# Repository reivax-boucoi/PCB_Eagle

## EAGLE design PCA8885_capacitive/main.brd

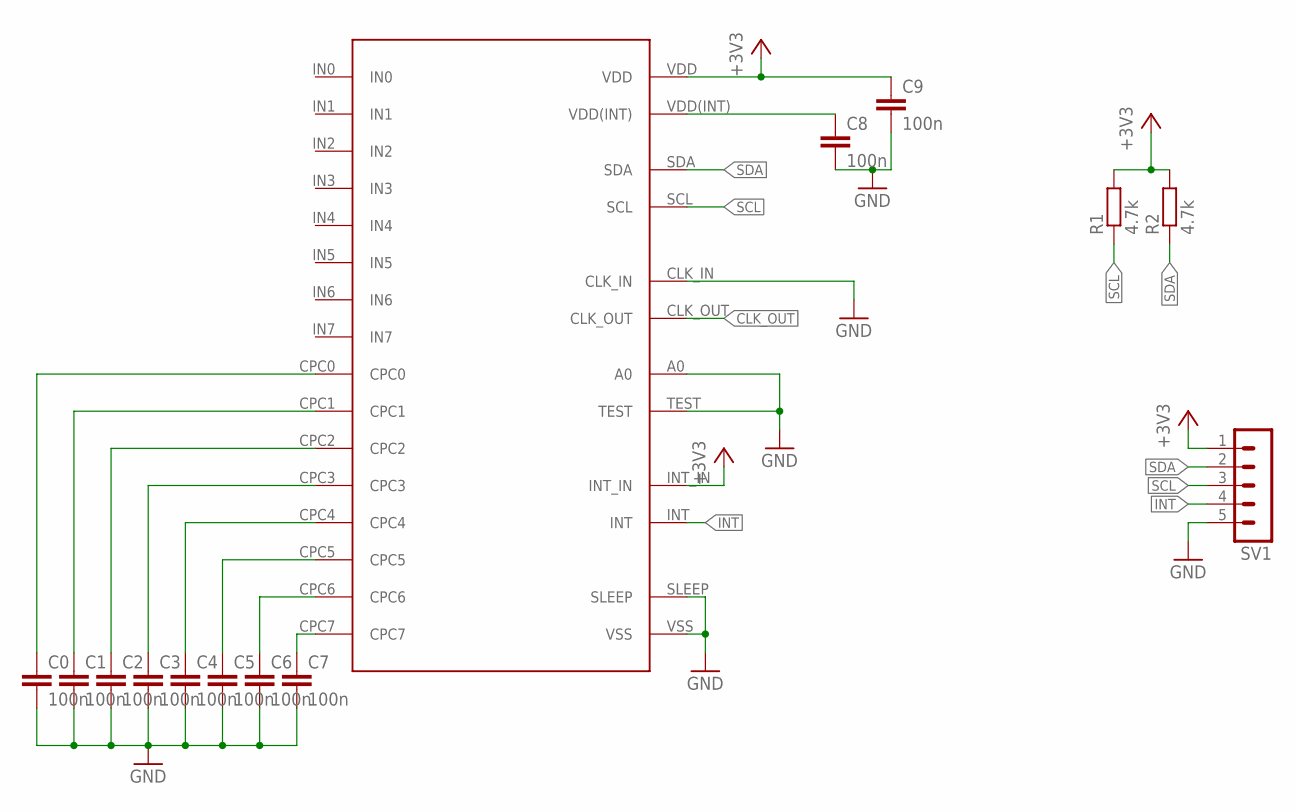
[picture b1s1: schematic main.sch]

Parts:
C0, C1, C2, C3, C4, C5, C6, C7, C8, C9: 100n; C0402
R1, R2: 4.7k; R0603
SV1: MA05-1
U$1: PCA8885; TSSOP28

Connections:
+3V3: C9.1, R1.2, R2.2, SV1.1, U$1.INT_IN, U$1.VDD
CLK_OUT: U$1.CLK_OUT
GND: C0.2, C1.2, C2.2, C3.2, C4.2, C5.2, C6.2, C7.2, C8.2, C9.2, SV1.5, U$1.A0, U$1.CLK_IN, U$1.SLEEP, U$1.TEST, U$1.VSS
INT: SV1.4, U$1.INT
unnamed: C7.1, U$1.CPC7
unnamed: C6.1, U$1.CPC6
unnamed: C5.1, U$1.CPC5
unnamed: C4.1, U$1.CPC4
unnamed: C3.1, U$1.CPC3
unnamed: C2.1, U$1.CPC2
unnamed: C1.1, U$1.CPC1
unnamed: C0.1, U$1.CPC0
unnamed: C8.1, U$1.VDD(INT)
SCL: R1.1, SV1.3, U$1.SCL
SDA: R2.1, SV1.2, U$1.SDA

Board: 2 copper layers, 14 parts (0 on the bottom side), 14 nets, no tracks yet.

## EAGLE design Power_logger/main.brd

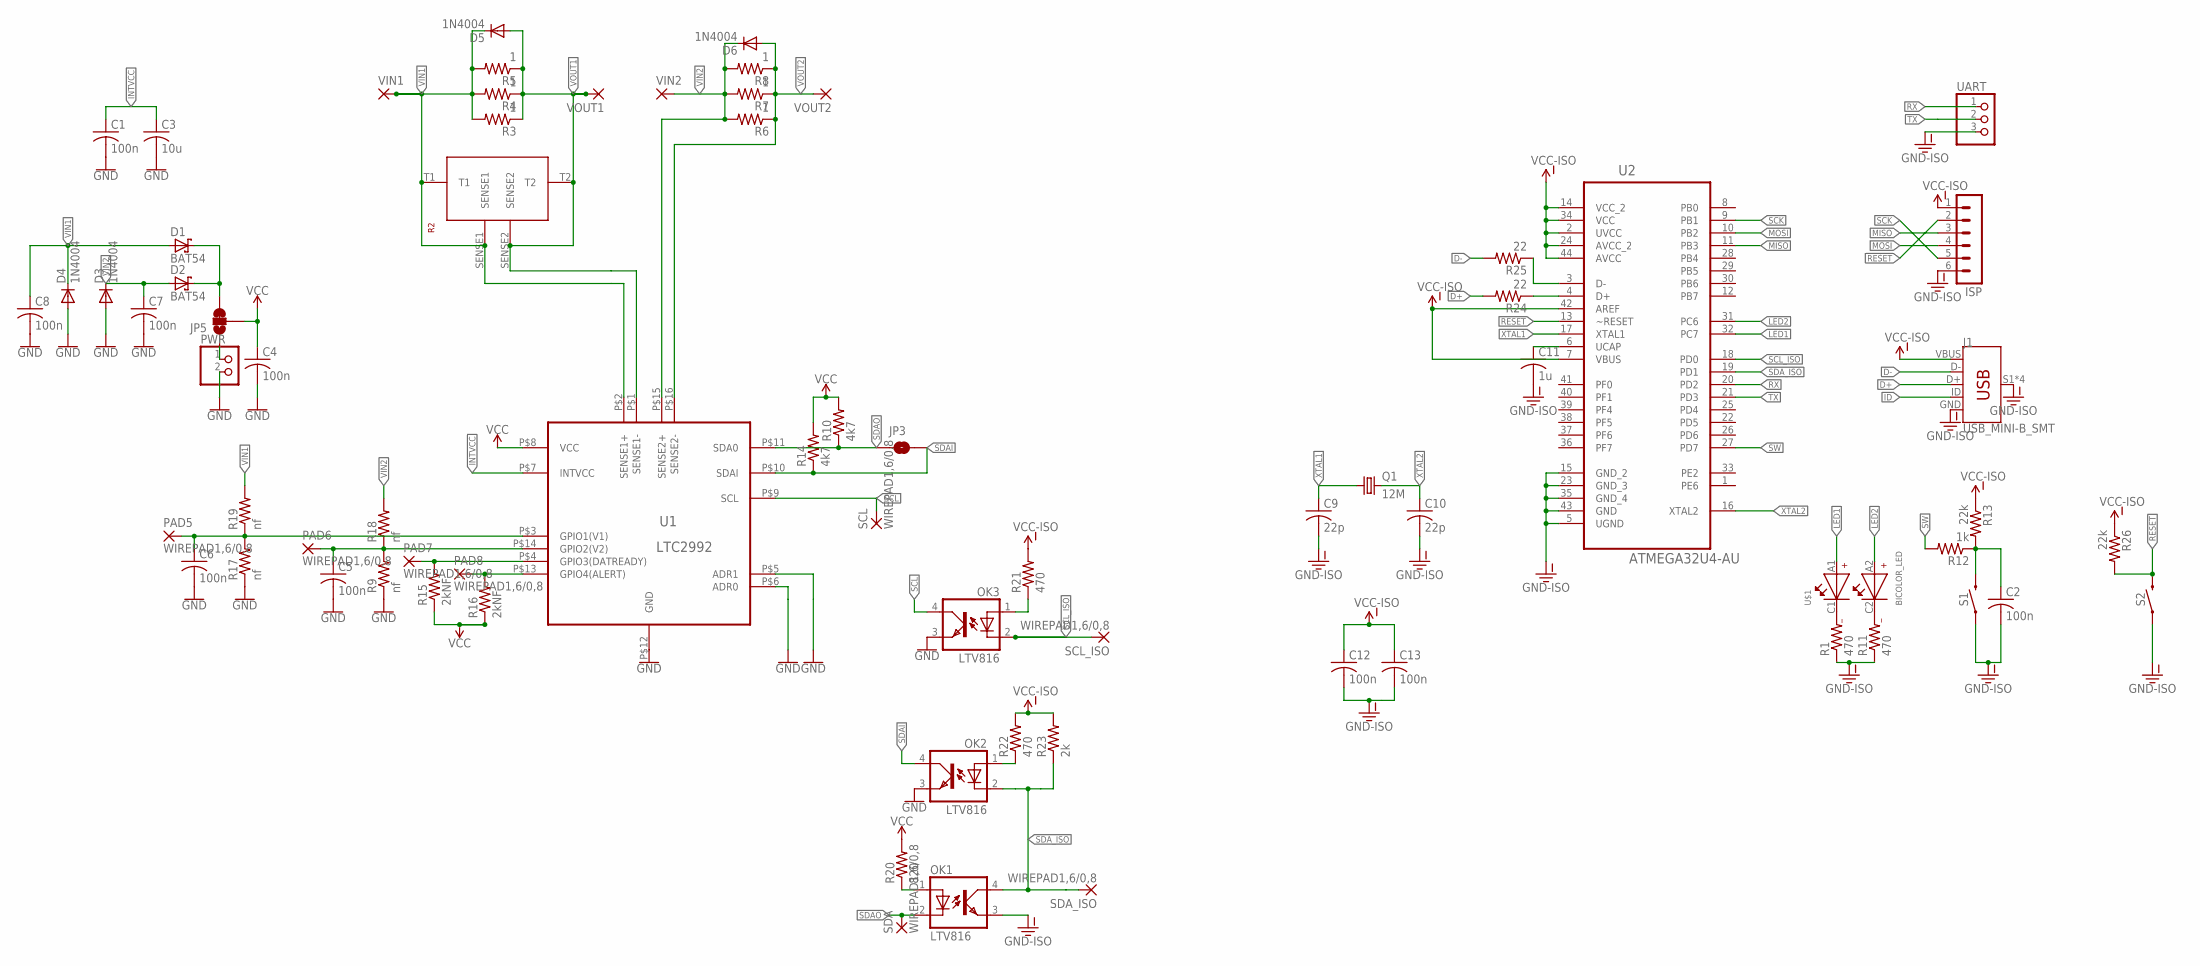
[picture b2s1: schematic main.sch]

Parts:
C1, C2, C4, C5, C6, C7, C8, C12, C13: 100n; C0603
C3: 10u; C0603
C9, C10: 22p; C0603
C11: 1u; C0603
D1, D2: BAT54; SOT23
D3, D4, D5, D6: 1N4004; DO41-10
ISP: MA06-1
J1: USB_MINI-B_SMT; USB-MINIB
JP3: JUMPER-SMT_2_NO_SILK; SMT-JUMPER_2_NO_SILK
JP5: JUMPER-SMT_3_1-NC_TRACE_NO-SILK; SMT-JUMPER_3_1-NC_TRACE_NO-SILK
OK1, OK2, OK3: LTV816; DIL04
PAD5, PAD6, PAD7, PAD8: WIREPAD1,6/0,8; 1,6/0,8
PWR: PINHD-1X2; 1X02
Q1: 12M; HC49/S
R1, R11, R21, R22: 470; R0603
R2: 30m; CSR2TTE30L0F
R3, R6: 1; 0309/12
R4, R7: 1; M1206
R5, R8: 1; R0603
R9, R17, R18, R19: nf; R0603
R10, R14: 4k7; R0603
R12: 1k; R0603
R13, R26: 22k; R0603
R15, R16: 2kNF; R0603
R20: 820; R0603
R23: 2k; R0603
R24, R25: 22; R0603
S1, S2: MOMENTARY-SWITCH-SPST-PTH-6.0MM-KIT; TACTILE_SWITCH_PTH_6.0MM_KIT
SCL: WIREPAD1,6/0,8; 1,6/0,8
SCL_ISO: WIREPAD1,6/0,8; 1,6/0,8
SDA: WIREPAD1,6/0,8; 1,6/0,8
SDA_ISO: WIREPAD1,6/0,8; 1,6/0,8
U1: LTC2992; MSOP_16
U2: ATMEGA32U4-AU; QFP80P1200X1200X120-44N
U$1: BICOLOR_LED
UART: PINHD-1X3; 1X03
VIN1, VIN2: 2,54/0,8
VOUT1, VOUT2: 2,54/0,8

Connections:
D+: J1.D+, R24.2
D-: J1.D-, R25.2
GND: C1.2, C3.2, C4.2, C5.2, C6.2, C7.2, C8.2, D3.A, D4.A, OK2.3 (EMIT), OK3.3 (EMIT), PWR.2, R9.1, R17.1, U1.P$5 (ADR1), U1.P$6 (ADR0), U1.P$12 (GND)
GND-ISO: C2.2, C9.2, C10.2, C11.2, C12.2, C13.2, ISP.6, J1.GND, J1.S1 (SHIELD), J1.S2 (SHIELD), J1.S3 (SHIELD), J1.S4 (SHIELD), OK1.3 (EMIT), R1.1, R11.1, S1.1, S2.1, U2.5 (UGND), U2.15 (GND_2), U2.23 (GND_3), U2.35 (GND_4), U2.43 (GND), UART.3
ID: J1.ID
INTVCC: C1.1, C3.1, U1.P$7 (INTVCC)
LED1: U2.32 (PC7), U$1.A1
LED2: U2.31 (PC6), U$1.A2
MISO: ISP.3, U2.11 (PB3)
MOSI: ISP.4, U2.10 (PB2)
unnamed: R1.2, U$1.C1
unnamed: R11.2, U$1.C2
unnamed: C2.1, R12.1, R13.2, S1.3 (2)
unnamed: OK1.1 (A), R20.1
unnamed: C6.1, PAD5.1, R17.2, R19.1, U1.P$3 (GPIO1(V1))
unnamed: C5.1, PAD6.1, R9.2, R18.1, U1.P$14 (GPIO2(V2))
unnamed: PAD7.1, R15.2, U1.P$4 (GPIO3(DATREADY))
unnamed: PAD8.1, R16.2, U1.P$13 (GPIO4(ALERT))
unnamed: JP5.1, PWR.1
unnamed: D1.3 (C), D2.3 (C), JP5.3
unnamed: OK3.1 (A), R21.1
unnamed: C11.1, U2.6 (UCAP)
unnamed: OK2.1 (A), R22.1
unnamed: R25.1, U2.3 (D-)
unnamed: R24.1, U2.4 (D+)
RESET: ISP.2, R26.2, S2.3 (2), U2.13 (~RESET)
RX: U2.20 (PD2), UART.1
SCK: ISP.5, U2.9 (PB1)
SCL: OK3.4 (COL), SCL.1, U1.P$9 (SCL)
SCL_ISO: OK3.2 (C), SCL_ISO.1, U2.18 (PD0)
SDAI: JP3.2, OK2.4 (COL), R14.1, U1.P$10 (SDAI)
SDAO: JP3.1, OK1.2 (C), R10.1, SDA.1, U1.P$11 (SDA0)
SDA_ISO: OK1.4 (COL), OK2.2 (C), R23.1, SDA_ISO.1, U2.19 (PD1)
SW: R12.2, U2.27 (PD7)
TX: U2.21 (PD3), UART.2
VCC: C4.1, JP5.2, R10.2, R14.2, R15.1, R16.1, R20.2, U1.P$8 (VCC)
VCC-ISO: C12.1, C13.1, ISP.1, J1.VBUS, R13.1, R21.2, R22.2, R23.2, R26.1, U2.2 (UVCC), U2.7 (VBUS), U2.14 (VCC_2), U2.24 (AVCC_2), U2.34 (VCC), U2.42 (AREF), U2.44 (AVCC)
VIN1: C8.1, D1.1 (A), D4.C, D5.C, R2.SENSE1, R2.T1, R3.2, R4.2, R5.2, R19.2, U1.P$2 (SENSE1+), VIN1.1
VIN2: C7.1, D2.1 (A), D3.C, D6.C, R6.2, R7.2, R8.2, R18.2, U1.P$15 (SENSE2+), VIN2.1
VOUT1: D5.A, R2.SENSE2, R2.T2, R3.1, R4.1, R5.1, U1.P$1 (SENSE1-), VOUT1.1
VOUT2: D6.A, R6.1, R7.1, R8.1, U1.P$16 (SENSE2-), VOUT2.1
XTAL1: C9.1, Q1.1, U2.17 (XTAL1)
XTAL2: C10.1, Q1.2, U2.16 (XTAL2)

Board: 2 copper layers, 72 parts (46 on the bottom side), 42 nets, no tracks yet.

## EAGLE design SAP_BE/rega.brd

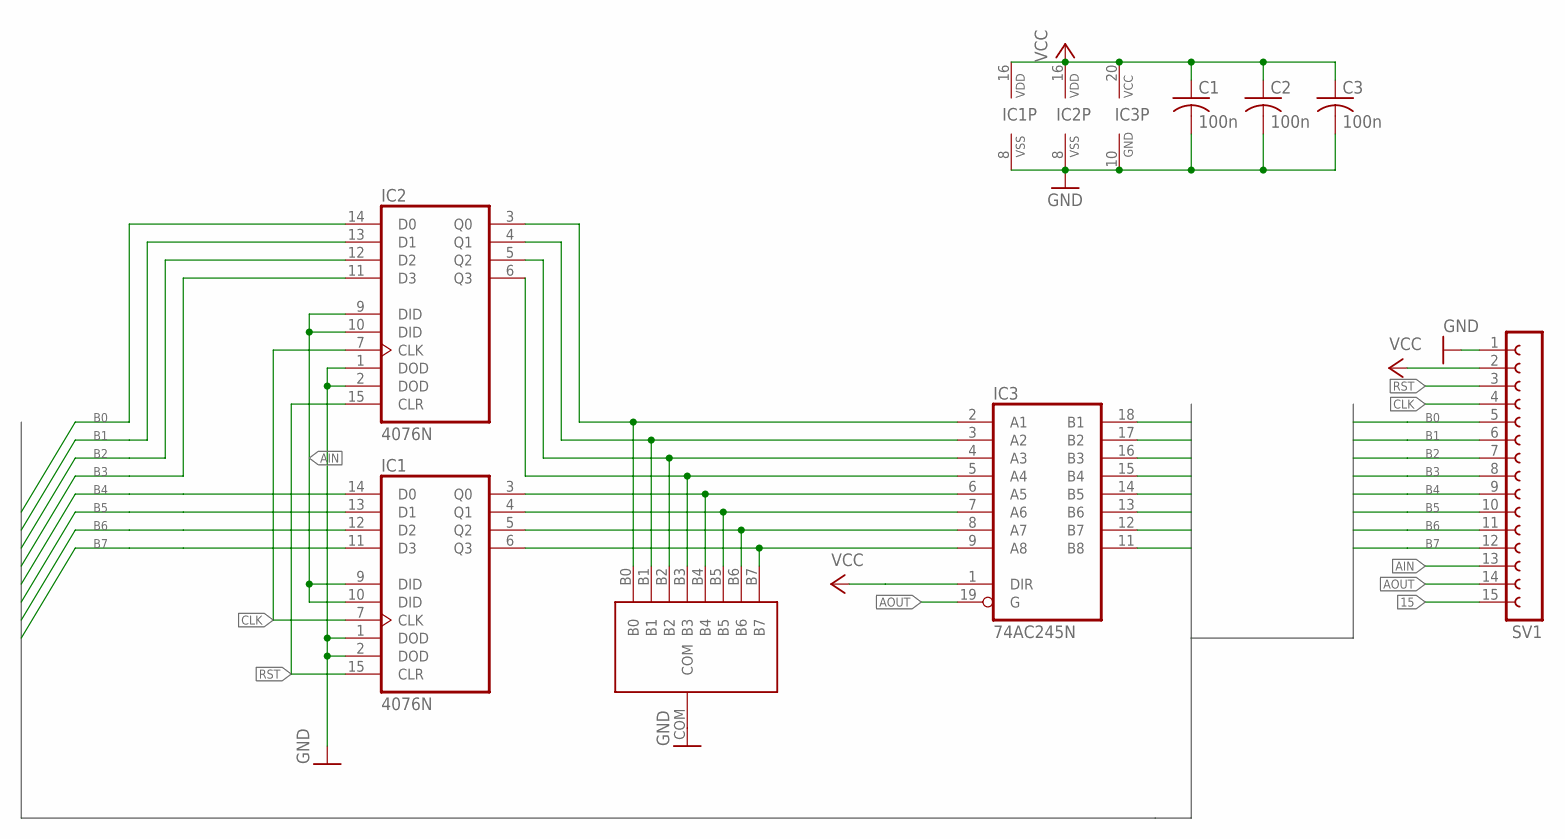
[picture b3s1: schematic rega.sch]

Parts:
C1, C2, C3: 100n; C050-025X075
IC1, IC2: 4076N; DIL16
IC3: 74AC245N; DIL20
SV1: FE15-1; FE15
U$1: LEDEDGEGRAPH

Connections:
15: SV1.15
AIN: IC1.9 (DID), IC1.10 (DID), IC2.9 (DID), IC2.10 (DID), SV1.13
AOUT: IC3.19 (G), SV1.14
B0: IC2.14 (D0), IC3.18 (B1), SV1.5
B1: IC2.13 (D1), IC3.17 (B2), SV1.6
B2: IC2.12 (D2), IC3.16 (B3), SV1.7
B3: IC2.11 (D3), IC3.15 (B4), SV1.8
B4: IC1.14 (D0), IC3.14 (B5), SV1.9
B5: IC1.13 (D1), IC3.13 (B6), SV1.10
B6: IC1.12 (D2), IC3.12 (B7), SV1.11
B7: IC1.11 (D3), IC3.11 (B8), SV1.12
CLK: IC1.7 (CLK), IC2.7 (CLK), SV1.4
GND: C1.2, C2.2, C3.2, IC1.1 (DOD), IC1.2 (DOD), IC1.8 (VSS), IC2.1 (DOD), IC2.2 (DOD), IC2.8 (VSS), IC3.10 (GND), SV1.1, U$1.COM
unnamed: IC1.3 (Q0), IC3.6 (A5), U$1.B4
unnamed: IC1.4 (Q1), IC3.7 (A6), U$1.B5
unnamed: IC1.5 (Q2), IC3.8 (A7), U$1.B6
unnamed: IC1.6 (Q3), IC3.9 (A8), U$1.B7
unnamed: IC2.6 (Q3), IC3.5 (A4), U$1.B3
unnamed: IC2.5 (Q2), IC3.4 (A3), U$1.B2
unnamed: IC2.4 (Q1), IC3.3 (A2), U$1.B1
unnamed: IC2.3 (Q0), IC3.2 (A1), U$1.B0
RST: IC1.15 (CLR), IC2.15 (CLR), SV1.3
VCC: C1.1, C2.1, C3.1, IC1.16 (VDD), IC2.16 (VDD), IC3.1 (DIR), IC3.20 (VCC), SV1.2

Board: 2 copper layers, 8 parts (0 on the bottom side), 22 nets, no tracks yet.

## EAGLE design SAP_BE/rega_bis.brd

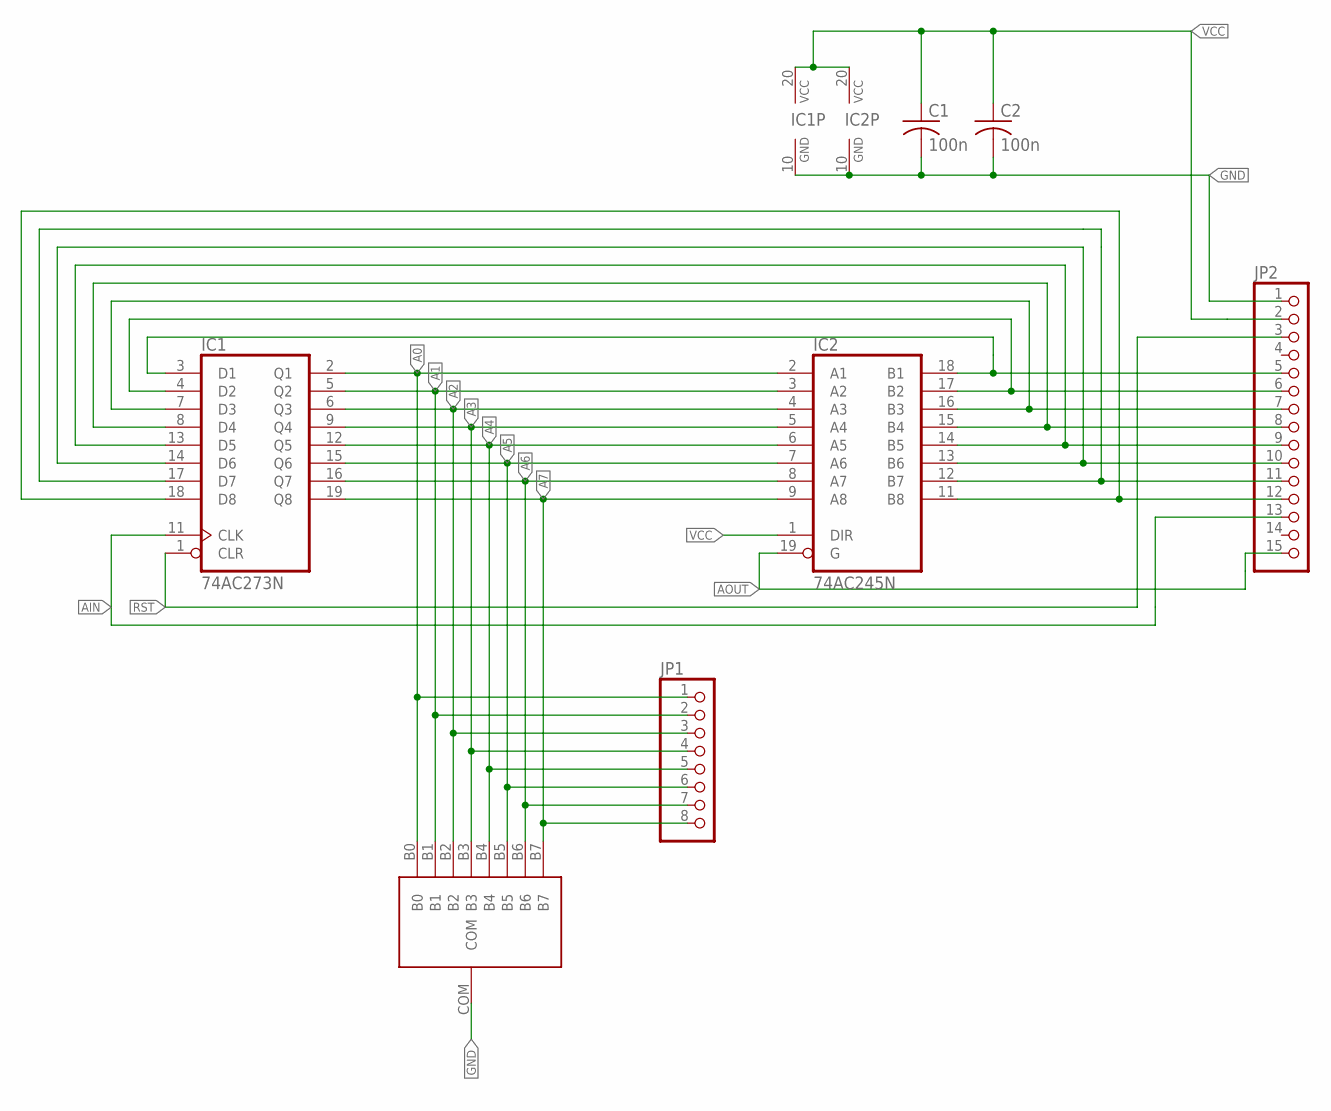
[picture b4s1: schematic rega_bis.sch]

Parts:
C1, C2: 100n; C050-025X075
IC1: 74AC273N; DIL20
IC2: 74AC245N; DIL20
JP1: PINHD-1X8; 1X08
JP2: PINHD-1X15/90; 1X15/90
U$1: LEDEDGEGRAPH

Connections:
A0: IC1.2 (Q1), IC2.2 (A1), JP1.1, U$1.B0
A1: IC1.5 (Q2), IC2.3 (A2), JP1.2, U$1.B1
A2: IC1.6 (Q3), IC2.4 (A3), JP1.3, U$1.B2
A3: IC1.9 (Q4), IC2.5 (A4), JP1.4, U$1.B3
A4: IC1.12 (Q5), IC2.6 (A5), JP1.5, U$1.B4
A5: IC1.15 (Q6), IC2.7 (A6), JP1.6, U$1.B5
A6: IC1.16 (Q7), IC2.8 (A7), JP1.7, U$1.B6
A7: IC1.19 (Q8), IC2.9 (A8), JP1.8, U$1.B7
AIN: IC1.11 (CLK), JP2.13
AOUT: IC2.19 (G), JP2.15
GND: C1.2, C2.2, IC1.10 (GND), IC2.10 (GND), JP2.1, U$1.COM
unnamed: IC1.8 (D4), IC2.15 (B4), JP2.8
unnamed: IC1.13 (D5), IC2.14 (B5), JP2.9
unnamed: IC1.14 (D6), IC2.13 (B6), JP2.10
unnamed: IC1.17 (D7), IC2.12 (B7), JP2.11
unnamed: IC1.18 (D8), IC2.11 (B8), JP2.12
RST: IC1.1 (CLR), JP2.3
VCC: C1.1, C2.1, IC1.20 (VCC), IC2.1 (DIR), IC2.20 (VCC), JP2.2
W0: IC1.3 (D1), IC2.18 (B1), JP2.5
W1: IC1.4 (D2), IC2.17 (B2), JP2.6
W2: IC1.7 (D3), IC2.16 (B3), JP2.7

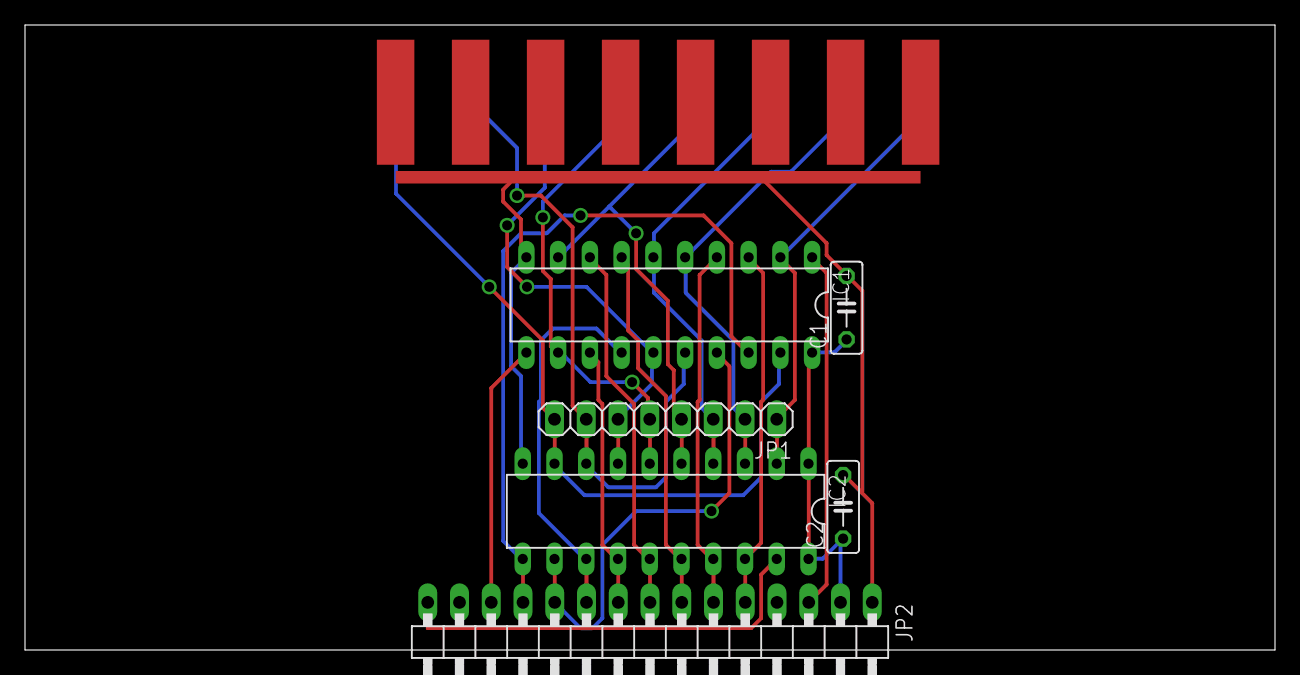
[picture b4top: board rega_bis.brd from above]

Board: 2 copper layers, 100.0 x 50.0 mm, 7 parts (1 on the bottom side), 21 nets.

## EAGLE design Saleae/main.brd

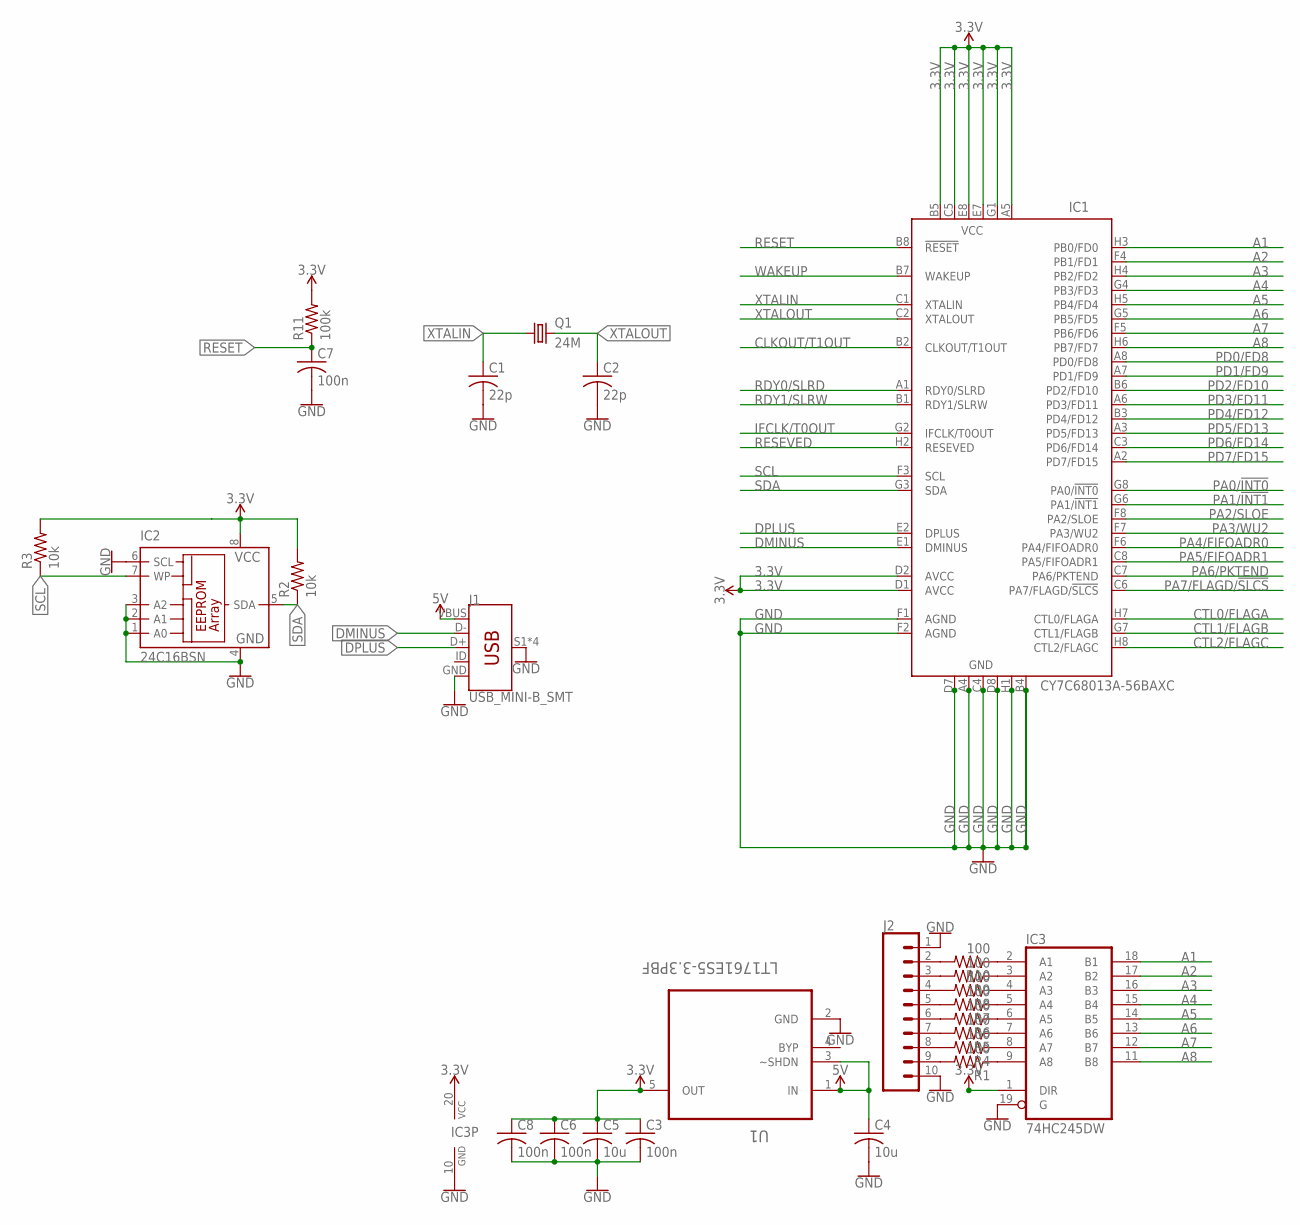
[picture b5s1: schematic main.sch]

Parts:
C1, C2: 22p; C0201
C3, C6, C7, C8: 100n; C0201
C4, C5: 10u; C0603K
IC1: CY7C68013A-56BAXC; VFBGA56
IC2: 24C16BSN; SO-08
IC3: 74HC245DW; SO20W
J1: USB_MINI-B_SMT; USB-MINIB
J2: CONN_10SMD; 1X10_SMD
Q1: 24M; CSM-7X-DU
R1, R4, R5, R6, R7, R8, R9, R10: 100; R0201
R2, R3: 10k; R0201
R11: 100k; R0201
U1: LT1761ES5-3.3PBF; SOT95P280X100-5N

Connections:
3.3V: C3.1, C5.1, C6.1, C8.1, IC1.A5 (VCC), IC1.B5 (VCC), IC1.C5 (VCC), IC1.D1 (AVCC), IC1.D2 (AVCC), IC1.E7 (VCC), IC1.E8 (VCC), IC1.G1 (VCC), IC2.8 (VCC), IC3.1 (DIR), IC3.20 (VCC), R2.2, R3.2, R11.2, U1.5 (OUT)
5V: C4.1, J1.VBUS, U1.1 (IN), U1.3 (~SHDN)
A1: IC1.H3 (PB0/FD0), IC3.18 (B1)
A2: IC1.F4 (PB1/FD1), IC3.17 (B2)
A3: IC1.H4 (PB2/FD2), IC3.16 (B3)
A4: IC1.G4 (PB3/FD3), IC3.15 (B4)
A5: IC1.H5 (PB4/FD4), IC3.14 (B5)
A6: IC1.G5 (PB5/FD5), IC3.13 (B6)
A7: IC1.F5 (PB6/FD6), IC3.12 (B7)
A8: IC1.H6 (PB7/FD7), IC3.11 (B8)
CLKOUT/T1OUT: IC1.B2 (CLKOUT/T1OUT)
CTL0/FLAGA: IC1.H7 (CTL0/FLAGA)
CTL1/FLAGB: IC1.G7 (CTL1/FLAGB)
CTL2/FLAGC: IC1.H8 (CTL2/FLAGC)
DMINUS: IC1.E1 (DMINUS), J1.D-
DPLUS: IC1.E2 (DPLUS), J1.D+
GND: C1.2, C2.2, C3.2, C4.2, C5.2, C6.2, C7.2, C8.2, IC1.A4 (GND), IC1.B4 (GND), IC1.C4 (GND), IC1.D7 (GND), IC1.D8 (GND), IC1.F1 (AGND), IC1.F2 (AGND), IC1.H1 (GND), IC2.1 (A0), IC2.2 (A1), IC2.3 (A2), IC2.4 (GND), IC2.6 (SCL), IC3.10 (GND), IC3.19 (G), J1.GND, J1.S1 (SHIELD), J1.S2 (SHIELD), J1.S3 (SHIELD), J1.S4 (SHIELD), J2.1, J2.10, U1.2 (GND)
IFCLK/T0OUT: IC1.G2 (IFCLK/T0OUT)
unnamed: IC3.9 (A8), R1.1
unnamed: IC3.8 (A7), R4.1
unnamed: IC3.7 (A6), R5.1
unnamed: IC3.6 (A5), R6.1
unnamed: IC3.5 (A4), R7.1
unnamed: IC3.4 (A3), R8.1
unnamed: IC3.3 (A2), R9.1
unnamed: IC3.2 (A1), R10.1
unnamed: J2.9, R1.2
unnamed: J2.8, R4.2
unnamed: J2.7, R5.2
unnamed: J2.6, R6.2
unnamed: J2.5, R7.2
unnamed: J2.4, R8.2
unnamed: J2.3, R9.2
unnamed: J2.2, R10.2
PA0/!INT0: IC1.G8 (PA0/!INT0)
PA1/!INT1: IC1.G6 (PA1/!INT1)
PA2/SLOE: IC1.F8 (PA2/SLOE)
PA3/WU2: IC1.F7 (PA3/WU2)
PA4/FIFOADR0: IC1.F6 (PA4/FIFOADR0)
PA5/FIFOADR1: IC1.C8 (PA5/FIFOADR1)
PA6/PKTEND: IC1.C7 (PA6/PKTEND)
PA7/FLAGD/!SLCS: IC1.C6 (PA7/FLAGD/!SLCS)
PD0/FD8: IC1.A8 (PD0/FD8)
PD1/FD9: IC1.A7 (PD1/FD9)
PD2/FD10: IC1.B6 (PD2/FD10)
PD3/FD11: IC1.A6 (PD3/FD11)
PD4/FD12: IC1.B3 (PD4/FD12)
PD5/FD13: IC1.A3 (PD5/FD13)
PD6/FD14: IC1.C3 (PD6/FD14)
PD7/FD15: IC1.A2 (PD7/FD15)
RDY0/SLRD: IC1.A1 (RDY0/SLRD)
RDY1/SLRW: IC1.B1 (RDY1/SLRW)
RESET: C7.1, IC1.B8 (!RESET), R11.1
RESEVED: IC1.H2 (RESEVED)
SCL: IC1.F3 (SCL), IC2.7 (WP), R3.1
SDA: IC1.G3 (SDA), IC2.5 (SDA), R2.1
WAKEUP: IC1.B7 (WAKEUP)
XTALIN: C1.1, IC1.C1 (XTALIN), Q1.1
XTALOUT: C2.1, IC1.C2 (XTALOUT), Q1.2

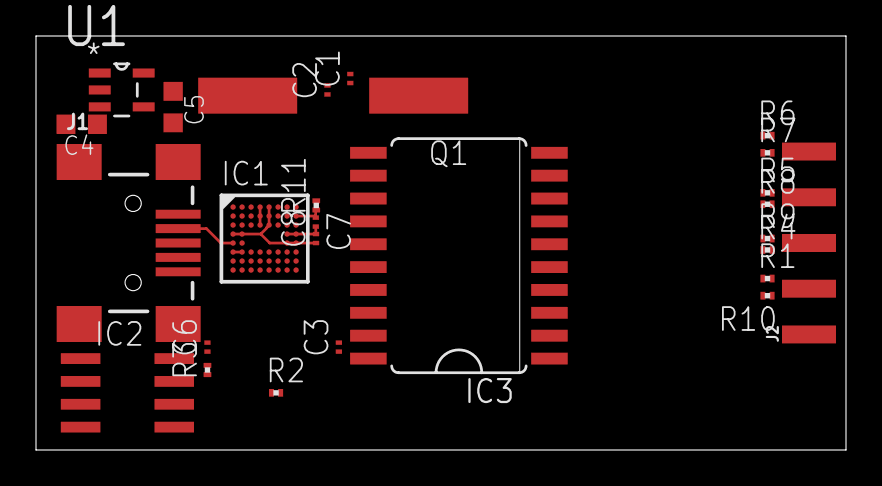
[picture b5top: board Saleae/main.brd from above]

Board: 2 copper layers, 45.0 x 23.0 mm, 26 parts (0 on the bottom side), 34 nets.

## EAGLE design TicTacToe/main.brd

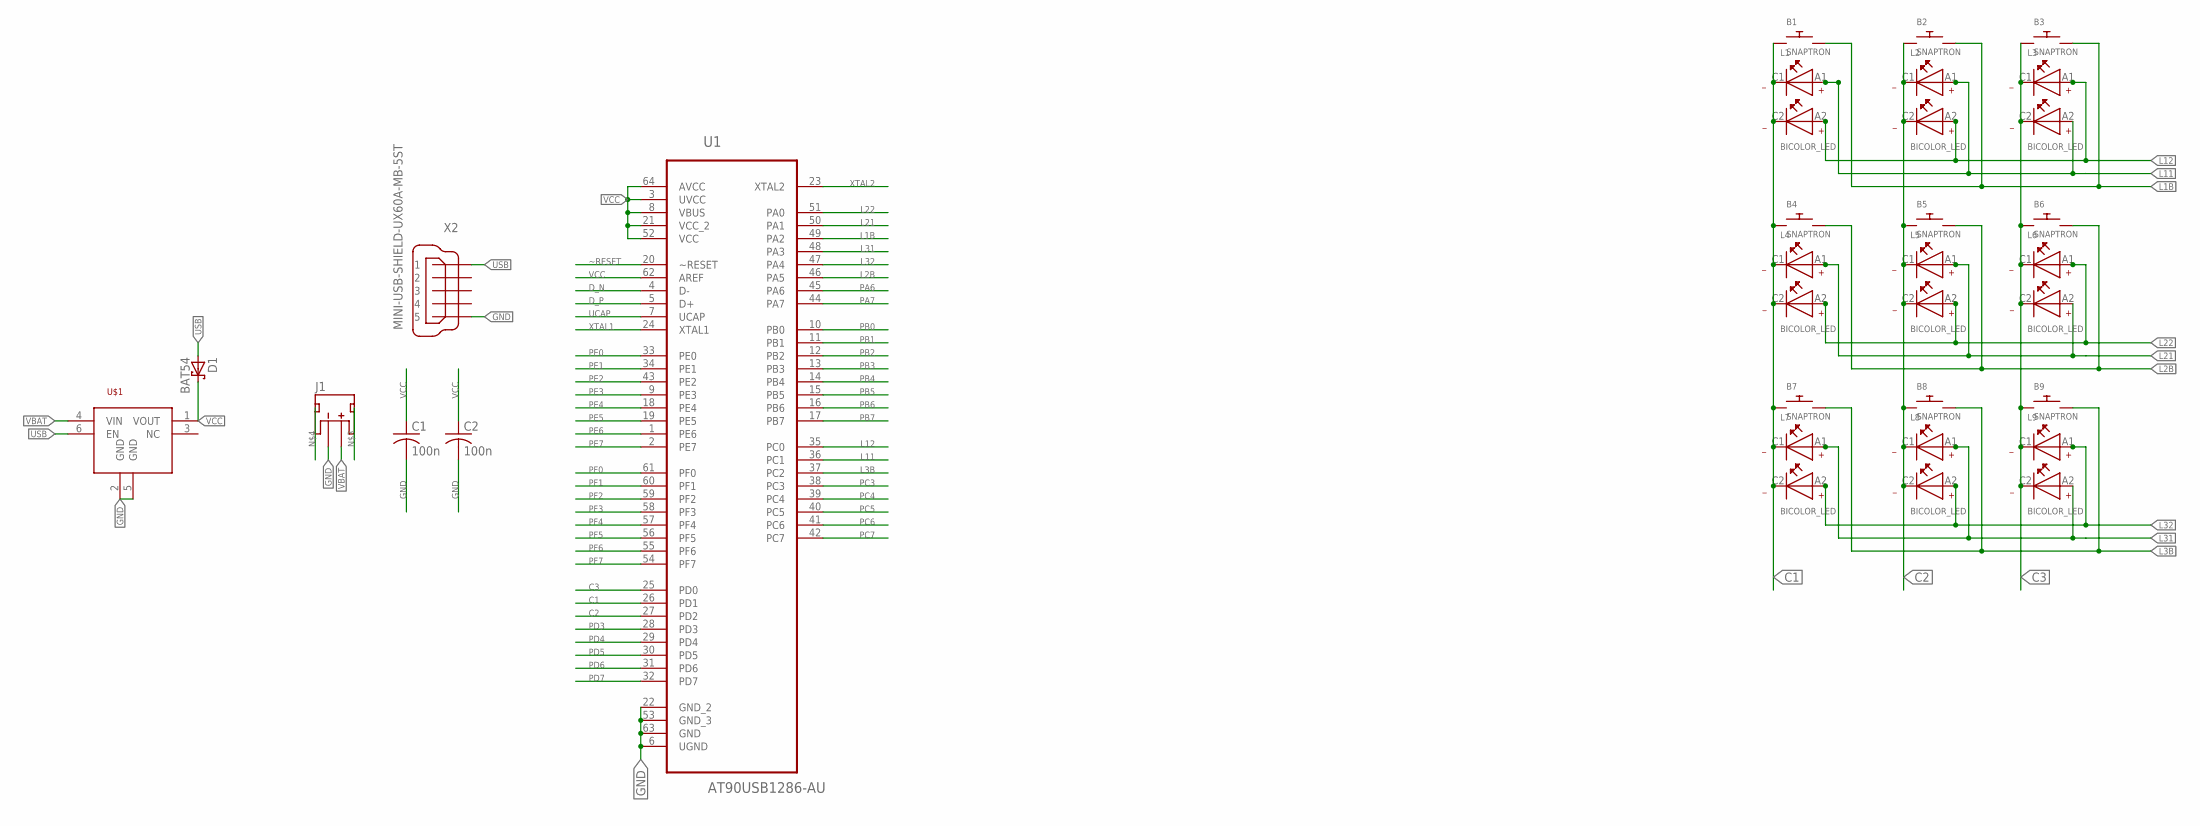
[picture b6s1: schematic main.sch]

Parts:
B1, B2, B3, B4, B5, B6, B7, B8, B9: SNAPTRON; SNAPTRON-8.5
C1, C2: 100n; C0603
D1: BAT54; SOT23
J1: JST_2MM_MALE; JST-2-SMD
L1, L2, L3, L4, L5, L6, L7, L8, L9: BICOLOR_LED
U1: AT90USB1286-AU; QFP80P1600X1600X120-64N
U$1: MIC94090; SC70-6L
X2: MINI-USB-SHIELD-UX60A-MB-5ST; UX60A-MB-5ST

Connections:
C1: B1.P$1, B4.P$1, B7.P$1, L1.C1, L1.C2, L4.C1, L4.C2, L7.C1, L7.C2, U1.26 (PD1)
C2: B2.P$1, B5.P$1, B8.P$1, L2.C1, L2.C2, L5.C1, L5.C2, L8.C1, L8.C2, U1.27 (PD2)
C3: B3.P$1, B6.P$1, B9.P$1, L3.C1, L3.C2, L6.C1, L6.C2, L9.C1, L9.C2, U1.25 (PD0)
D_N: U1.4 (D-)
D_P: U1.5 (D+)
GND: C1.2, C2.2, J1.1 (-), U1.6 (UGND), U1.22 (GND_2), U1.53 (GND_3), U1.63 (GND), U$1.2 (GND), U$1.5 (GND), X2.5
L1B: B1.P$2, B2.P$2, B3.P$2, U1.49 (PA2)
L2B: B4.P$2, B5.P$2, B6.P$2, U1.46 (PA5)
L3B: B7.P$2, B8.P$2, B9.P$2, U1.37 (PC2)
L11: L1.A1, L2.A1, L3.A2, U1.36 (PC1)
L12: L1.A2, L2.A2, L3.A1, U1.35 (PC0)
L21: L4.A1, L5.A1, L6.A2, U1.50 (PA1)
L22: L4.A2, L5.A2, L6.A1, U1.51 (PA0)
L31: L7.A1, L8.A1, L9.A2, U1.48 (PA3)
L32: L7.A2, L8.A2, L9.A1, U1.47 (PA4)
PA6: U1.45 (PA6)
PA7: U1.44 (PA7)
PB0: U1.10 (PB0)
PB1: U1.11 (PB1)
PB2: U1.12 (PB2)
PB3: U1.13 (PB3)
PB4: U1.14 (PB4)
PB5: U1.15 (PB5)
PB6: U1.16 (PB6)
PB7: U1.17 (PB7)
PC3: U1.38 (PC3)
PC4: U1.39 (PC4)
PC5: U1.40 (PC5)
PC6: U1.41 (PC6)
PC7: U1.42 (PC7)
PD3: U1.28 (PD3)
PD4: U1.29 (PD4)
PD5: U1.30 (PD5)
PD6: U1.31 (PD6)
PD7: U1.32 (PD7)
PE0: U1.33 (PE0)
PE1: U1.34 (PE1)
PE2: U1.43 (PE2)
PE3: U1.9 (PE3)
PE4: U1.18 (PE4)
PE5: U1.19 (PE5)
PE6: U1.1 (PE6)
PE7: U1.2 (PE7)
PF0: U1.61 (PF0)
PF1: U1.60 (PF1)
PF2: U1.59 (PF2)
PF3: U1.58 (PF3)
PF4: U1.57 (PF4)
PF5: U1.56 (PF5)
PF6: U1.55 (PF6)
PF7: U1.54 (PF7)
UCAP: U1.7 (UCAP)
USB: D1.1 (A), U$1.6 (EN), X2.1
VBAT: J1.2 (+), U$1.4 (VIN)
VCC: C1.1, C2.1, D1.3 (C), U1.3 (UVCC), U1.8 (VBUS), U1.21 (VCC_2), U1.52 (VCC), U1.62 (AREF), U1.64 (AVCC), U$1.1 (VOUT)
XTAL1: U1.24 (XTAL1)
XTAL2: U1.23 (XTAL2)
~RESET: U1.20 (~RESET)

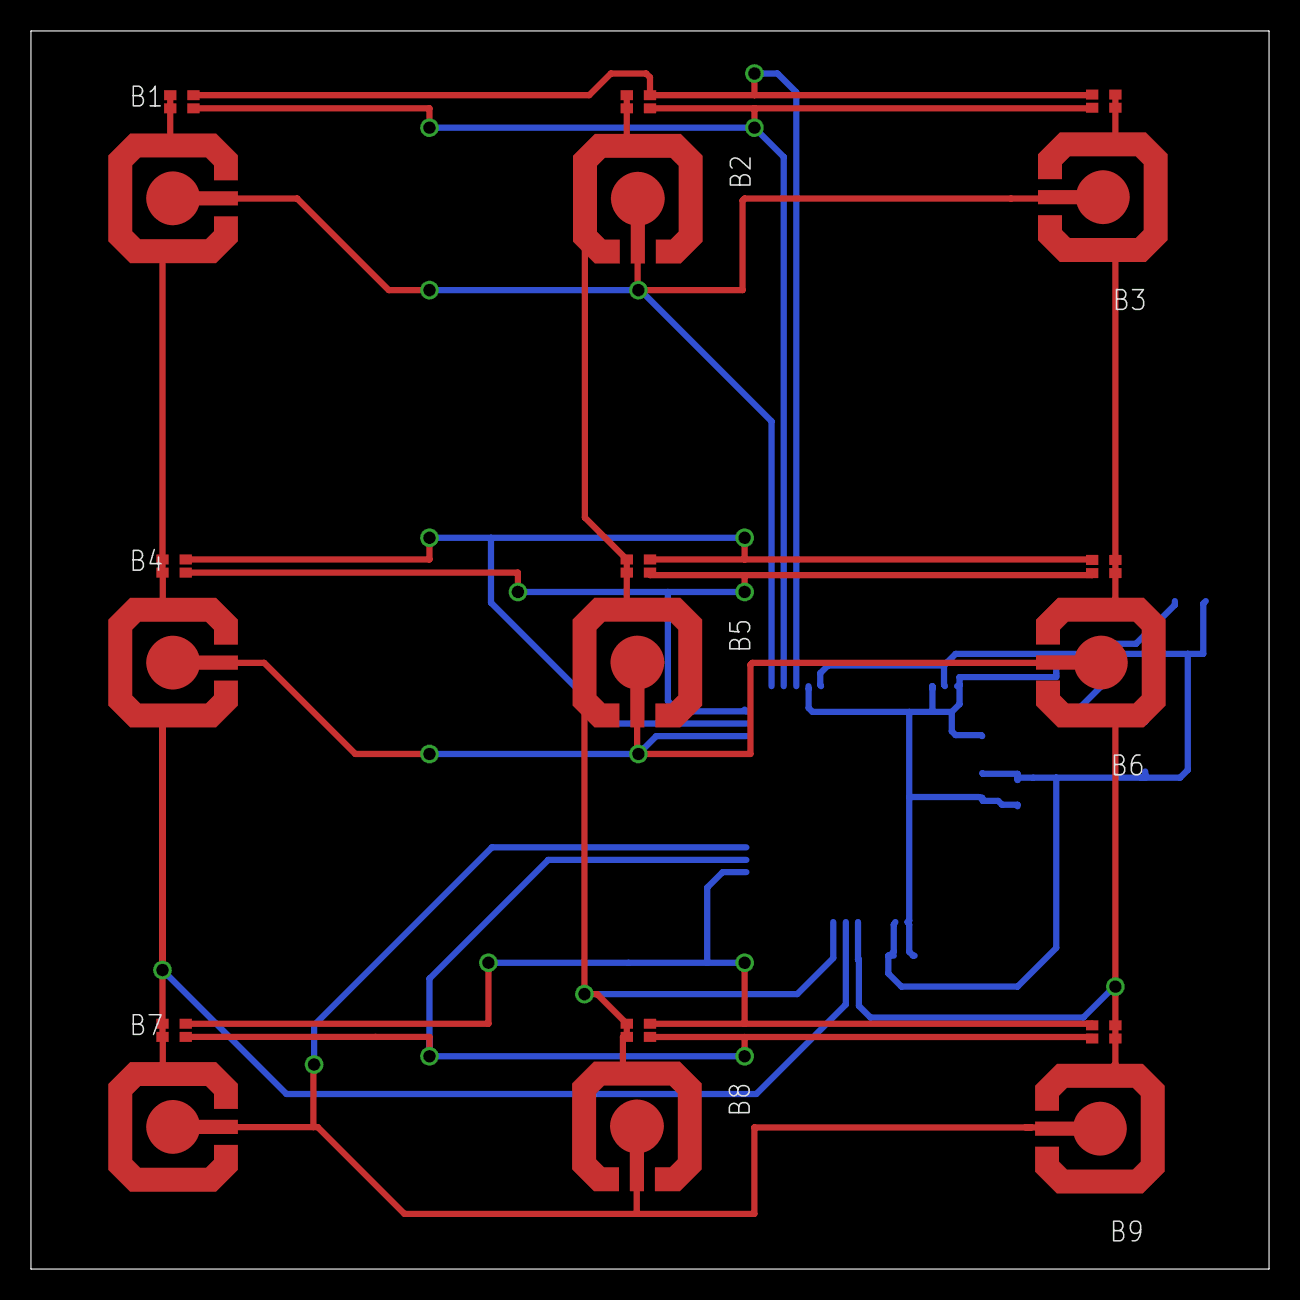
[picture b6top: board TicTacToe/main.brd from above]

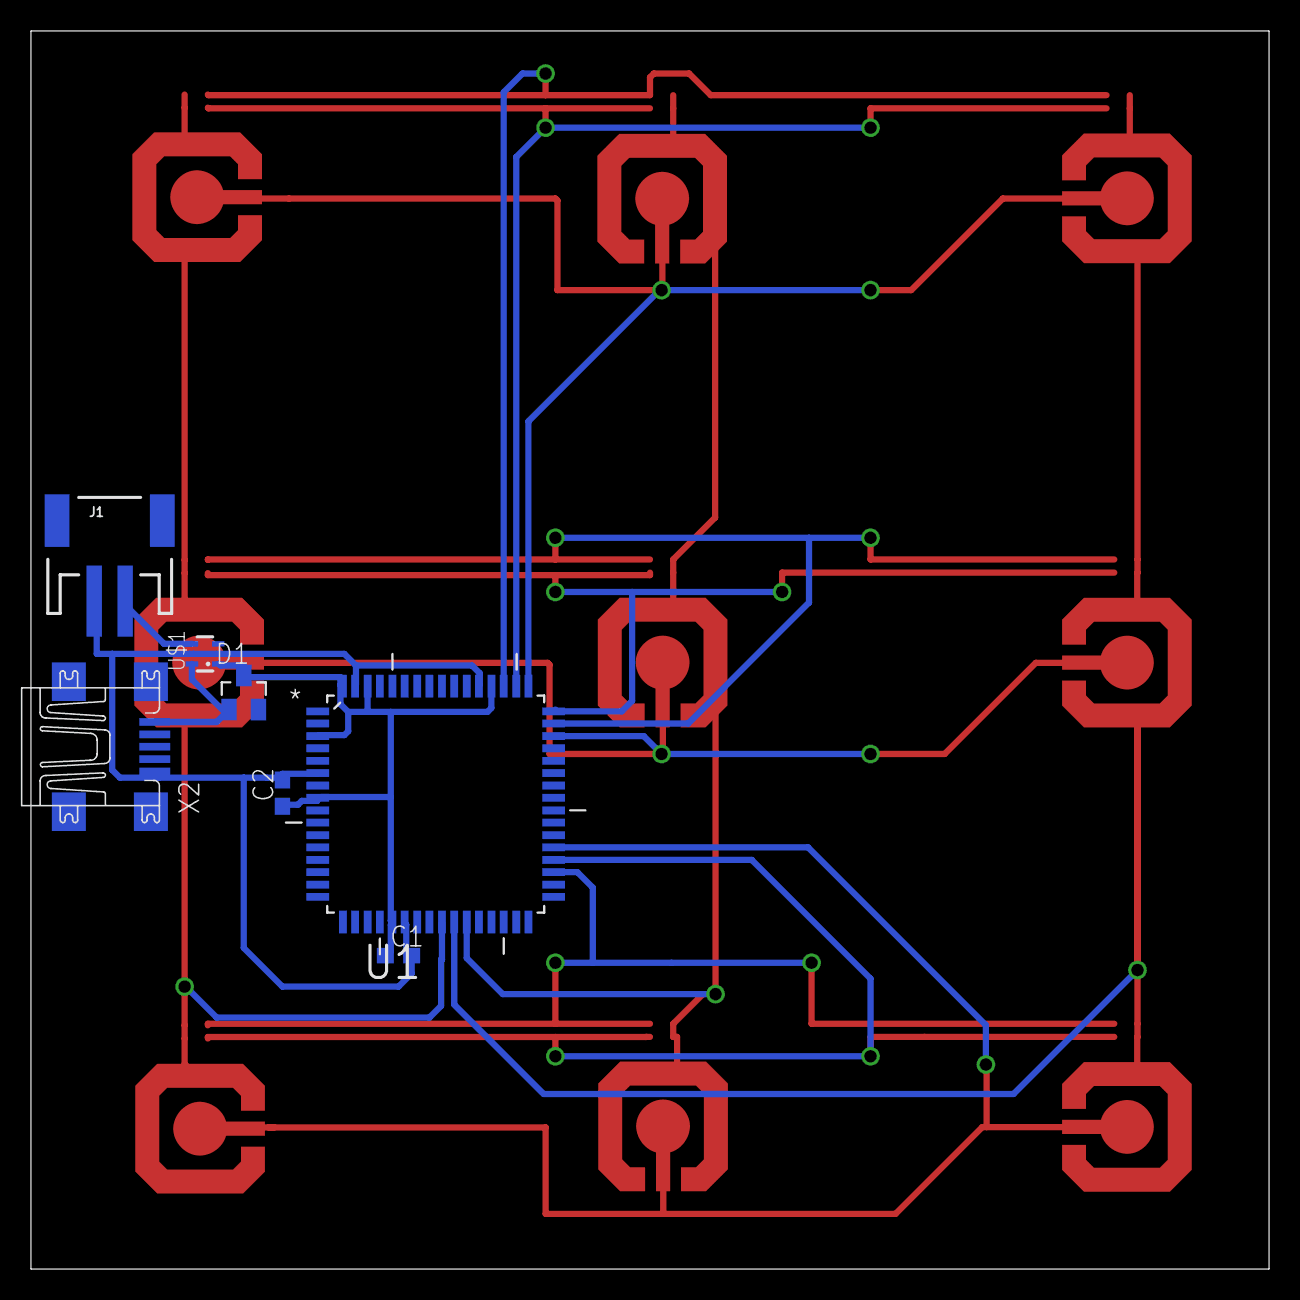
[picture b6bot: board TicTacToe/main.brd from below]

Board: 2 copper layers, 80.0 x 80.0 mm, 25 parts (7 on the bottom side), 16 nets.

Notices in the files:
parts and their libraries:
SparkFun-Connectors: Licensing: Creative Commons ShareAlike 4.0 International - https://creativecommons.org/licenses/by-sa/4.0
